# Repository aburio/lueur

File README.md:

# Lueur

This repository contain the source code & hardware design of the lueur project. Lueur is a pair of internet connected cubes who can light up each other using an ESP8266, an RGB LED and AWS IoT.

## Build with

* [Platformio](https://platformio.org/)
* [ESP8266 core for Arduino](https://github.com/esp8266/Arduino)
* [ESPAsyncWebServer](https://github.com/me-no-dev/ESPAsyncWebServer)
* [ESPAsyncTCP](https://github.com/me-no-dev/ESPAsyncTCP)
* [pubsubclient](https://github.com/knolleary/pubsubclient)

## License

This project is licensed under the MIT License - see the [LICENSE.md](LICENSE.md) file for details

## Authors

* [Clément Aceituno](https://github.com/clementAC) - Captive portal & OTA webpage source code
* [Arthur Burnichon](https://github.com/aburio) - Firmware source code & PCB design
* Loïc Badel - Casing design

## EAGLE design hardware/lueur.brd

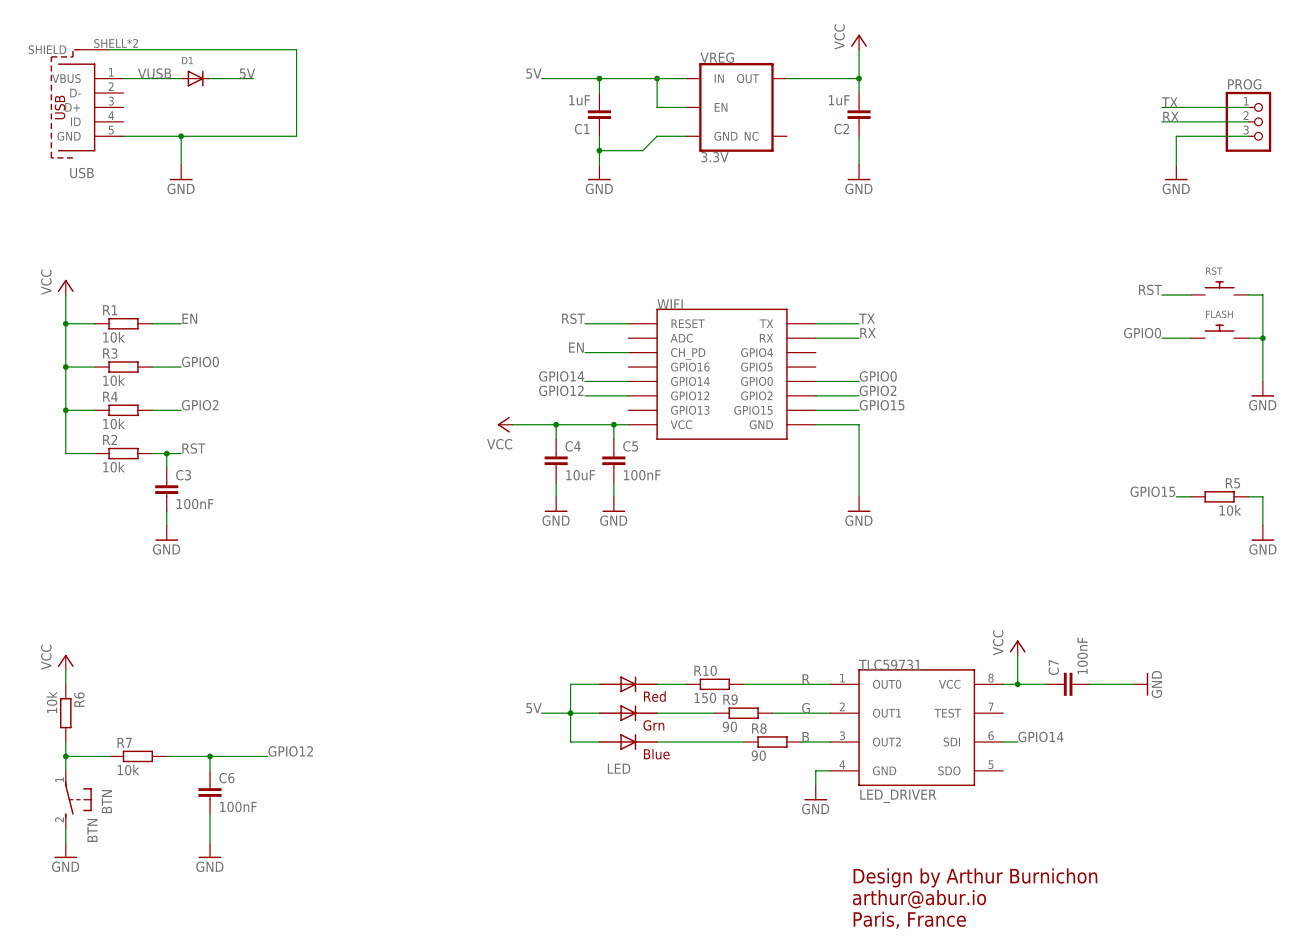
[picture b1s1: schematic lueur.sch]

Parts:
BTN: BTN; B3F-31XX
C1, C2: 1uF; C0805
C3, C5, C6, C7: 100nF; C0805
C4: 10uF; C0805
D1: DIODESMA; SMADIODE
FLASH: SWITCH_PUSHBUTTONSOFTTOUCHSMD_SJ; PUSHBUTTON_SMD_SJ
LED: RGB5555; RGBLED5050
LED_DRIVER: TLC59731; SOIC8
PROG: PINHD-1X3; 1X03
R1, R2, R3, R4, R5, R6, R7: 10k; R0805
R8, R9: 90; R0805
R10: 150; R0805
RST: SWITCH_PUSHBUTTONSOFTTOUCHSMD_SJ; PUSHBUTTON_SMD_SJ
USB: 614105150721
VREG: 3.3V; SOT23-5
WIFI: ESP12SMD; ESP12-SMD

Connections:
5V: C1.2, D1.C, LED.4 (RED_A), LED.5 (GREEN_A), LED.6 (BLUE_A), VREG.1 (IN), VREG.3 (EN)
B: LED_DRIVER.3 (OUT2), R8.2
BTN: BTN.1, R6.2, R7.1
EN: R1.2, WIFI.CH_PD
G: LED_DRIVER.2 (OUT1), R9.2
GND: BTN.2 (S), C1.1, C2.1, C3.2, C4.2, C5.2, C6.2, C7.2, FLASH.P$2, LED_DRIVER.4 (GND), PROG.3, R5.1, RST.P$2, USB.5 (GND), USB.SHELL (SHIELD), USB.SHELL1 (SHIELD), VREG.2 (GND), WIFI.GND
GPIO0: FLASH.P$1, R3.2, WIFI.GPIO0
GPIO2: R4.2, WIFI.GPIO2
GPIO12: C6.1, R7.2, WIFI.GPIO12
GPIO14: LED_DRIVER.6 (SDI), WIFI.GPIO14
GPIO15: R5.2, WIFI.GPIO15
unnamed: LED.3 (RED_C), R10.1
unnamed: LED.2 (GREEN_C), R9.1
unnamed: LED.1 (BLUE_C), R8.1
R: LED_DRIVER.1 (OUT0), R10.2
RST: C3.1, R2.2, RST.P$1, WIFI.RESET
RX: PROG.2, WIFI.RXD0 (RX)
TX: PROG.1, WIFI.TXD0 (TX)
VCC: C2.2, C4.1, C5.1, C7.1, LED_DRIVER.8 (VCC), R1.1, R2.1, R3.1, R4.1, R6.1, VREG.5 (OUT), WIFI.VCC
VUSB: D1.A, USB.1 (VBUS)

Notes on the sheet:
Design by Arthur Burnichon arthur@abur.io Paris, France

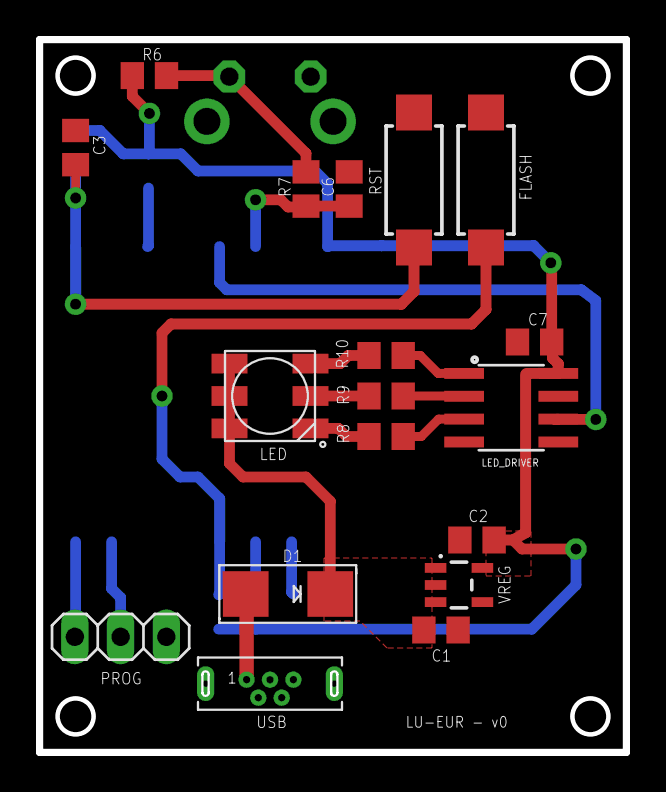
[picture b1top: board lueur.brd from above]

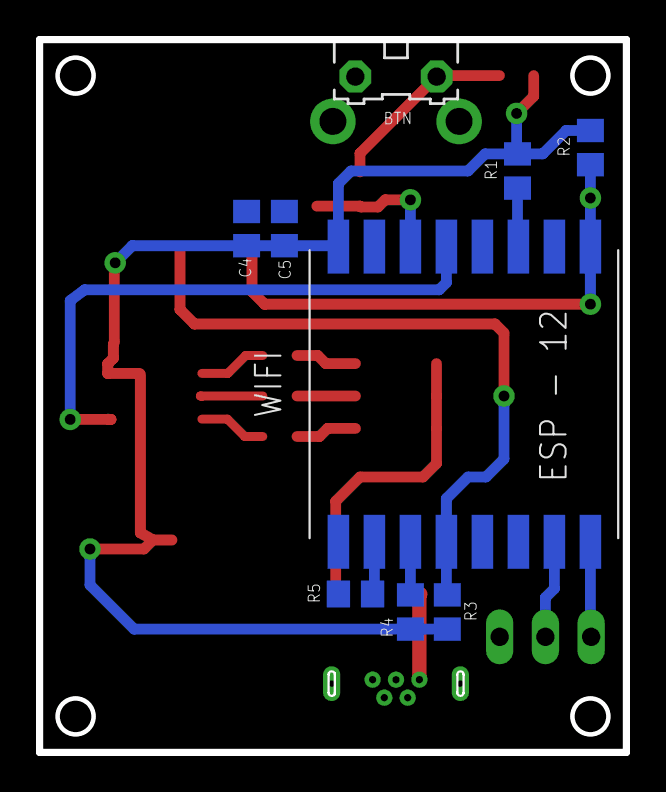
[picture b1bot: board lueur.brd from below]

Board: 2 copper layers, 32.6 x 39.6 mm, 27 parts (9 on the bottom side), 20 nets.

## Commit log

2020-02-26 📩 Import of the Lueur project from Luseed (www.luseed.io) Bitbucket private repository to Github
2020-02-26 📸 Fix of the README image

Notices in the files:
parts and their libraries:
SparkFun-IC-Power: Licensing: Creative Commons ShareAlike 4.0 International - https://creativecommons.org/licenses/by-sa/4.0
EAGLE-INPUT_OUTPUT_CONNECTORS-rev16c: Copyright: Würth Elektronik
